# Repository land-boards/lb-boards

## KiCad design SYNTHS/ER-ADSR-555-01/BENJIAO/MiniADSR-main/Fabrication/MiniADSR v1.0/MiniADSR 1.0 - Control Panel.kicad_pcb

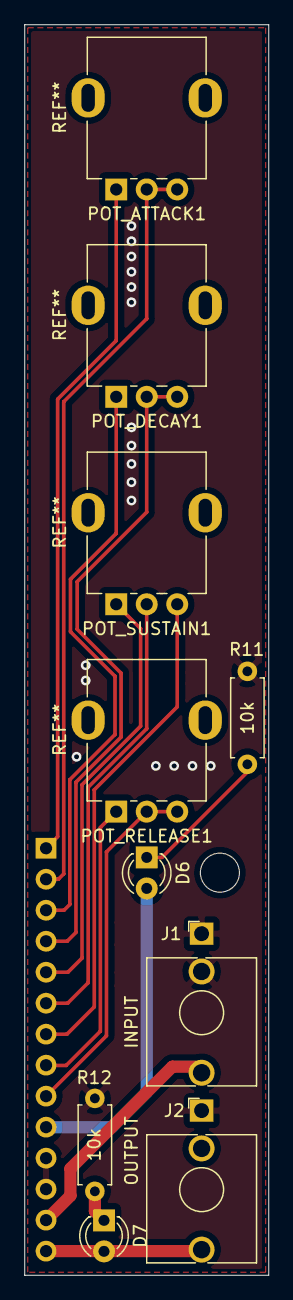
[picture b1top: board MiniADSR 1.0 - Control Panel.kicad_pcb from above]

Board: 2 copper layers, 20.0 x 102.5 mm, 11 parts (1 on the bottom side), 15 nets.

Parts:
D6: PWR_LED; LED_D3.0mm
D7: OUTPUT_LED; LED_D3.0mm
J1: INPUT; AudioJack_3.5mm
J2: OUTPUT; AudioJack_3.5mm
J4: ControlBoard_Pins; PinSocket_1x14_P2.54mm_Vertical
POT_ATTACK1: 1M; Potentiometer_RV09
POT_DECAY1: 1M; Potentiometer_RV09
POT_RELEASE1: 1M; Potentiometer_RV09
POT_SUSTAIN1: 1M; Potentiometer_RV09
R11, R12: 10k; R_Axial_DIN0207_L6.3mm_D2.5mm_P7.62mm_Horizontal

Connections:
A1: J1.T, J4.13
A2: D7.2, J2.T, J4.14
A3: J4.1, POT_ATTACK1.1
A4: J4.2, POT_ATTACK1.2, POT_ATTACK1.3
A5: J4.3, POT_DECAY1.1
A6: J4.4, POT_DECAY1.2, POT_DECAY1.3
A7: J4.5, POT_SUSTAIN1.1
A8: J4.6, POT_SUSTAIN1.2
A9: J4.7, POT_SUSTAIN1.3
A10: J4.8, POT_RELEASE1.1
A11: J4.9, POT_RELEASE1.2, POT_RELEASE1.3
A_VCC: D6.2, J4.10
GND1: J1.S, J1.TN, J2.S, J4.11, J4.12, R11.1, R12.1
unnamed: D6.1, R11.2
unnamed: D7.1, R12.2

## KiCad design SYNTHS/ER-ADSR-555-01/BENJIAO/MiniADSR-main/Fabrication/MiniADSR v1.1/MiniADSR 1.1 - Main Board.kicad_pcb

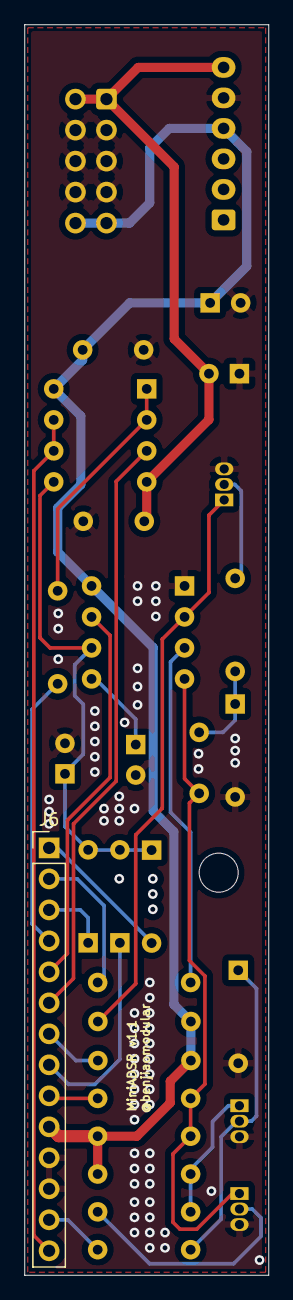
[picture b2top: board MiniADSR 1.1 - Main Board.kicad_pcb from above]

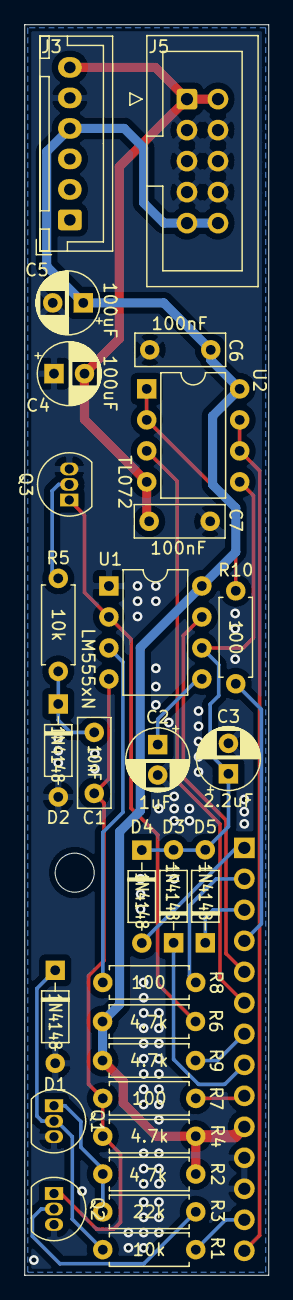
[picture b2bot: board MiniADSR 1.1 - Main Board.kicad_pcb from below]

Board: 2 copper layers, 20.0 x 102.5 mm, 30 parts (29 on the bottom side), 25 nets.

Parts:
C1: 10nF; C_Rect_L7.2mm_W2.5mm_P5.00mm_FKS2_FKP2_MKS2_MKP2
C2: 1uF; CP_Radial_D5.0mm_P2.50mm
C3: 2.2uF; CP_Radial_D5.0mm_P2.50mm
C4, C5: 100uF; CP_Radial_D5.0mm_P2.50mm
C6, C7: 100nF; C_Rect_L7.2mm_W2.5mm_P5.00mm_FKS2_FKP2_MKS2_MKP2
D1, D2, D3, D4, D5: 1N4148; D_DO-35_SOD27_P7.62mm_Horizontal
J3: JST_BUS; JST_XH_B6B-XH-A_1x06_P2.50mm_Vertical
J5: IDC_BUS; IDC-Header_2x05_P2.54mm_Vertical
J6: MainBoard_Pins; PinHeader_1x14_P2.54mm_Vertical
Q1, Q2, Q3: BC547; TO-92_Inline
R1, R5: 10k; R_Axial_DIN0207_L6.3mm_D2.5mm_P7.62mm_Horizontal
R2, R4, R6, R9: 4.7k; R_Axial_DIN0207_L6.3mm_D2.5mm_P7.62mm_Horizontal
R3: 22k; R_Axial_DIN0207_L6.3mm_D2.5mm_P7.62mm_Horizontal
R7, R8, R10: 100; R_Axial_DIN0207_L6.3mm_D2.5mm_P7.62mm_Horizontal
U1: LM555xN; DIP-8_W7.62mm
U2: TL072; DIP-8_W7.62mm

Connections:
+12V: C4.1, C6.1, J3.4, J5.9, J5.10, J6.10, R2.2, R4.2, R6.2, R9.2, U1.8, U2.8
-12V: C5.2, C7.2, J3.6, J5.1, J5.2, U2.4
B1: J6.13, R1.2
B2: J6.14, U2.6, U2.7
B3: D4.2, J6.1
B4: J6.2, R8.2
B5: D5.1, J6.3
B6: J6.4, R10.2
B7: J6.5, U1.7
B8: J6.6, U2.3
B9: J6.7, R9.1
B10: D3.1, J6.8
B11: J6.9, R7.2
GND2: C2.2, C3.2, C4.2, C5.1, C6.2, C7.1, D1.2, D2.2, J3.5, J5.3, J5.4, J5.5, J5.6, J5.7, J5.8, J6.11, J6.12, Q1.3, Q2.3, Q3.3, U1.1
unnamed: C1.1, D2.1, R5.1
unnamed: C1.2, Q2.1, R4.1, R7.1, U1.4
unnamed: C2.1, U1.5
unnamed: C3.1, D3.2, D4.1, D5.2, U1.6, U2.5
unnamed: D1.1, Q1.2, R1.1
unnamed: Q1.1, R2.1, R3.1
unnamed: Q2.2, R3.2
unnamed: Q3.1, R6.1, U1.2
unnamed: Q3.2, R5.2
unnamed: R8.1, U1.3
unnamed: R10.1, U2.1, U2.2

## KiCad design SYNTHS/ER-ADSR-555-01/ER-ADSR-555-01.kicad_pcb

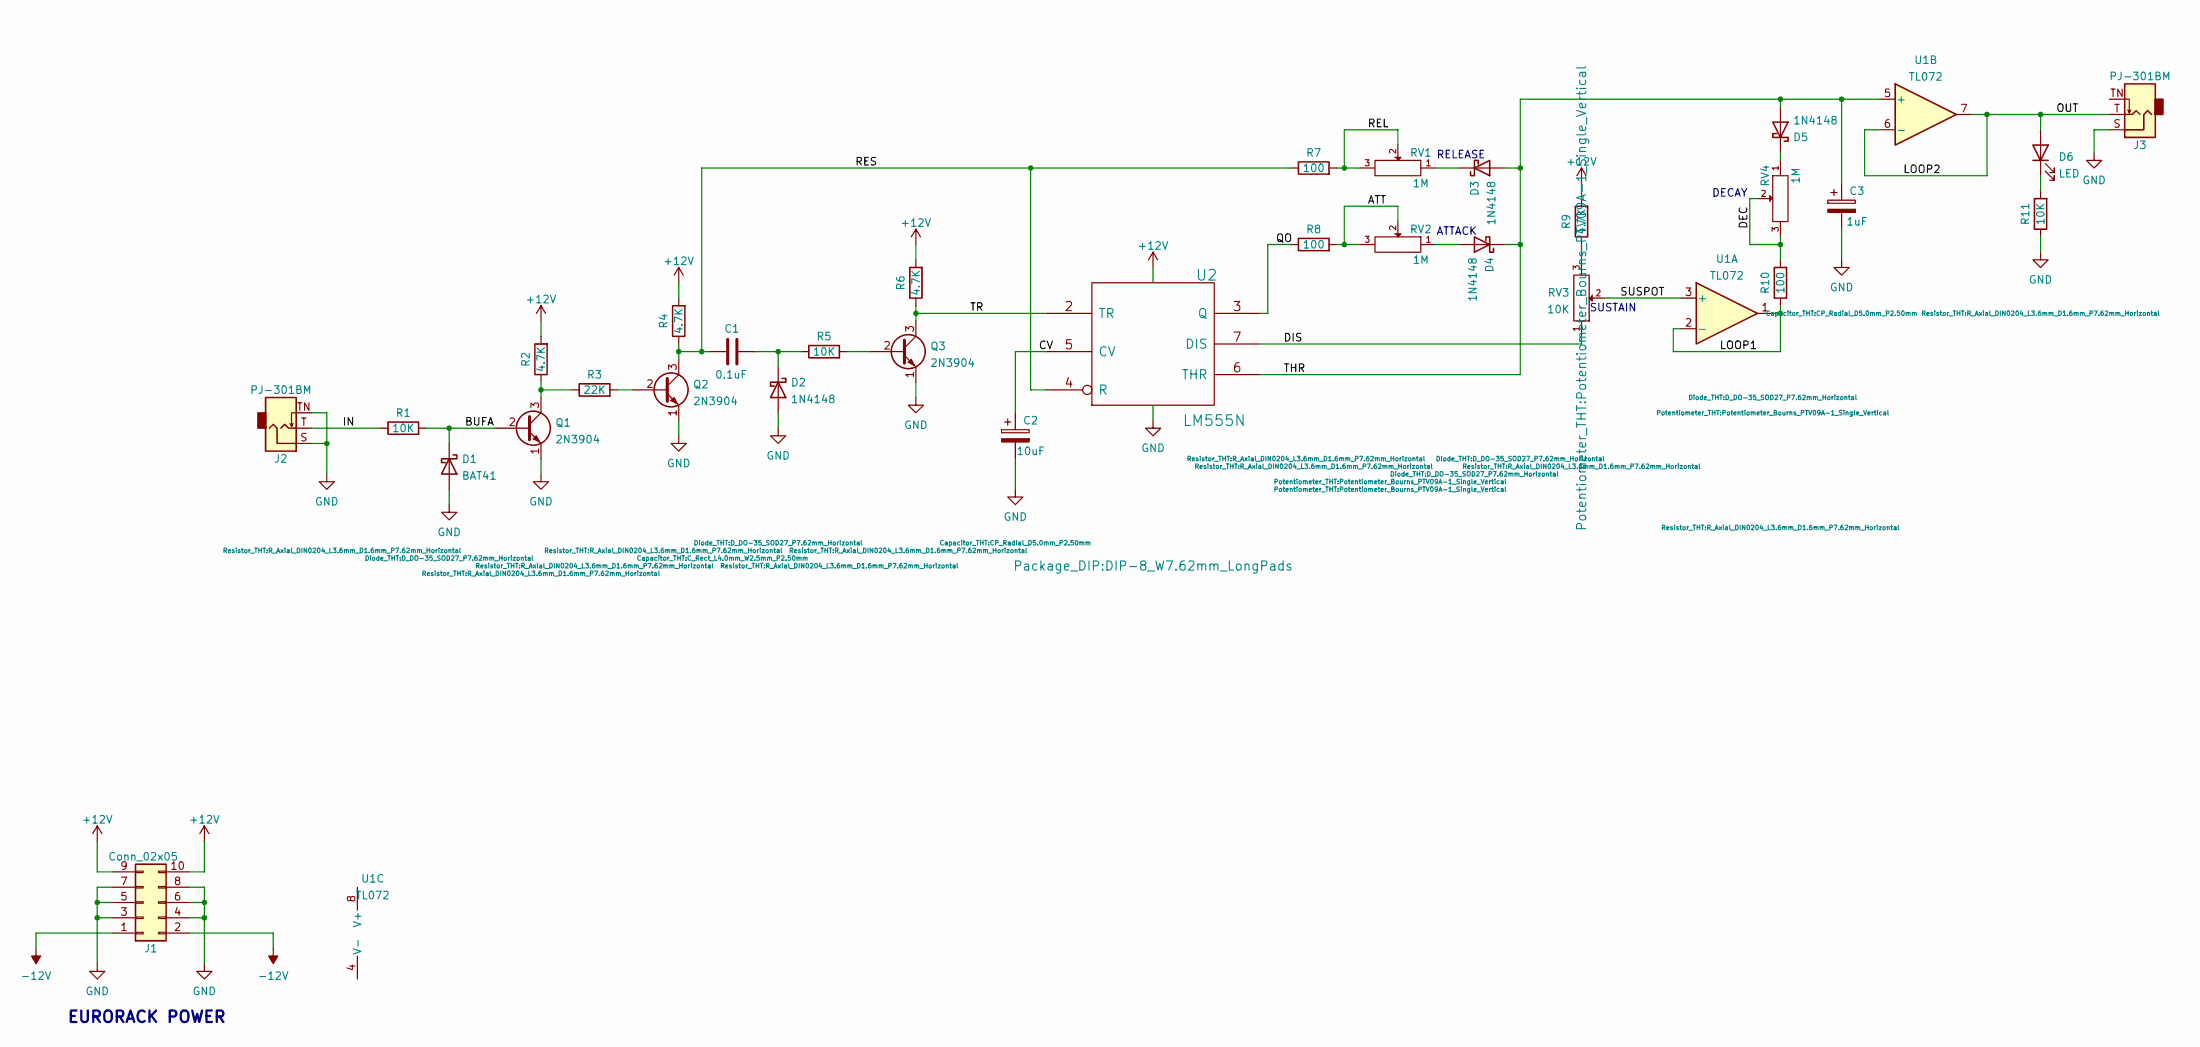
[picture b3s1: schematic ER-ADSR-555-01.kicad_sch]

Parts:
C1: 0.1uF; C_Rect_L4.0mm_W2.5mm_P2.50mm
C2: 10uF; CP_Radial_D5.0mm_P2.50mm
C3: 1uF; CP_Radial_D5.0mm_P2.50mm
D1: BAT41; D_DO-35_SOD27_P7.62mm_Horizontal
D2, D3, D4, D5: 1N4148; D_DO-35_SOD27_P7.62mm_Horizontal
D6: LED
J1: Conn_02x05; IDC-Header_2x05_P2.54mm_Vertical
J2, J3: PJ-301BM; Jack_3.5mm_QingPu_WQP-PJ301BM_Vertical
Q1, Q2, Q3: 2N3904; TO-92_Inline
R1, R5, R11: 10K; R_Axial_DIN0204_L3.6mm_D1.6mm_P7.62mm_Horizontal
R2, R4, R6, R9: 4.7K; R_Axial_DIN0204_L3.6mm_D1.6mm_P7.62mm_Horizontal
R3: 22K; R_Axial_DIN0204_L3.6mm_D1.6mm_P7.62mm_Horizontal
R7, R8, R10: 100; R_Axial_DIN0204_L3.6mm_D1.6mm_P7.62mm_Horizontal
RV1, RV2, RV4: 1M; Potentiometer_Bourns_PTV09A-1_Single_Vertical
RV3: 10K; Potentiometer_Bourns_PTV09A-1_Single_Vertical
U1: TL072; DIP-8_W7.62mm
U2: LM555N; DIP-8_W7.62mm_LongPads

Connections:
+12V: J1.9, J1.10, R2.2, R4.2, R6.2, R9.2, U2.8 (VCC)
-12V: J1.1, J1.2
/BUFA: D1.1 (K), Q1.2 (B), R1.2
/CV: C2.1, U2.5 (CV)
/DIS: RV3.1, U2.7 (DIS)
/IN: J2.T, R1.1
/LOOP1: R10.1, U1.1, U1.2 (-)
/OUT: D6.2 (A), J3.T, U1.6 (-), U1.7
/QO: R8.1, U2.3 (Q)
/RES: C1.1, Q2.3 (C), R4.1, R7.1, U2.4 (R)
/SUSPOT: RV3.2, U1.3 (+)
/THR: C3.1, D3.2 (A), D4.1 (K), D5.2 (A), U1.5 (+), U2.6 (THR)
/TR: Q3.3 (C), R6.1, U2.2 (TR)
GND: C2.2, C3.2, D1.2 (A), D2.2 (A), J1.3, J1.4, J1.5, J1.6, J1.7, J1.8, J2.S, J2.TN, J3.S, Q1.1 (E), Q2.1 (E), Q3.1 (E), R11.1, U2.1 (GND)
unnamed: C1.2, D2.1 (K), R5.1
unnamed: D3.1 (K), RV1.1
unnamed: D4.2 (A), RV2.1
unnamed: D5.1 (K), RV4.1
unnamed: D6.1 (K), R11.2
unnamed: Q1.3 (C), R2.1, R3.1
unnamed: Q2.2 (B), R3.2
unnamed: Q3.2 (B), R5.2
unnamed: R7.2, RV1.2, RV1.3
unnamed: R8.2, RV2.2, RV2.3
unnamed: R9.1, RV3.3
unnamed: R10.2, RV4.2, RV4.3

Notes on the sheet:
DECAY
EURORACK POWER
ATTACK
RELEASE
SUSTAIN

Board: 2 copper layers, 31 parts (0 on the bottom side), 25 nets, no tracks yet.
